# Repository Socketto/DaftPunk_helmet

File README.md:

# Project Overview

This project consists of two interconnected boards using the I2C protocol. The main board, equipped with a PIC microcontroller, controls RGB LEDs (used in the mask project for the ears) and a series of MCP23017 IO extenders for the screen positioned in front of the eyes.

Additionally, a 24LC256 EEPROM is included to store phrases to be displayed, which would otherwise be too short due to memory limitations.

## Programming and Interfaces

The board is programmed using a PicKit via an ICSP connector and can interface with RS485 networks or via an HC-06 module (Bluetooth).

## Android App Integration

The repository also includes a simple Android project that allows the board to be controlled via a smartphone. Through the app, users can:
- Display custom text on the screen
- Change the status of the RGB LEDs

[helmet](https://www.facebook.com/100001224670164/videos/a.159338040783684/2948037965246997?locale=it_IT)

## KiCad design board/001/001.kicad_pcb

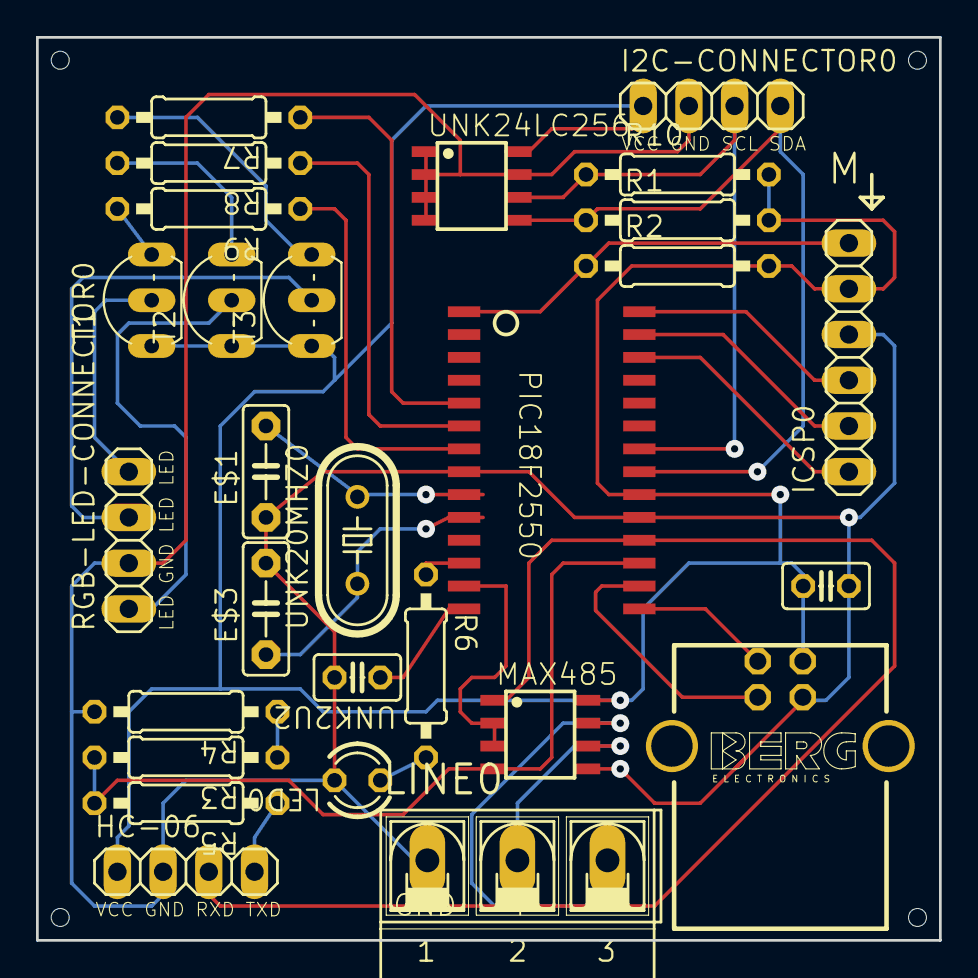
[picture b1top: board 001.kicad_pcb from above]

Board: 2 copper layers, 50.2 x 50.2 mm, 32 parts (0 on the bottom side), 10 nets.

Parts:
E$1, E$3: C5B2.5_116
HC-06: 1X04_325
I2C-CONNECTOR0: 1X04_325
ICSP0: 1X06_325
LED0: LED3MM_259
LINE0: AK500_3-H_181
MAX485: M8_279
PIC18F2550: SOIC28-3_206
R1, R2, R10: 10k; 0207_10_217
R3, R4, R5: 1k; 0207_10_217
R6, R7, R8, R9: 470; 0207_10_217
RGB-LED-CONNECTOR0: 1X04_325
T1, T2, T3: BC640; TO92-BCE_399
UNK2U2, UNK220UF0: C025-025X050_334
UNK20MHZ0: HC49_S_204
UNK24LC256: M8_279
UNK_HOLE_0: dummyfp0
UNK_HOLE_1: dummyfp1
UNK_HOLE_2: dummyfp2
UNK_HOLE_3: dummyfp3
USB0: PN61729-S_130

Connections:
S$1: R3.2, R5.2
S$2: HC-06.1, HC-06.2, I2C-CONNECTOR0.1, LED0.K, R4.2, R7.1, R8.1, R9.1, RGB-LED-CONNECTOR0.2, UNK2U2.2
S$5: I2C-CONNECTOR0.4, R1.1
S$12: R7.2, T3.B
S$16: R1.2, R10.2
S$23: R8.2, T2.B
S$25: HC-06.4, R5.1
S$27: R9.2, T1.B
S$29: RGB-LED-CONNECTOR0.1, T2.C
S$32: R3.1, R4.1

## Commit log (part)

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2025-03-07 [ADD] First commit
2025-03-07 [ADD] Add compilation of firmware
2025-03-07 Rename dotnet-desktop.yml to build-desktop.yml
2025-03-08 [FIX] Try fix compilation error with old compiler XC8
2025-03-09 Rename mplab-x_2.yml to mplab-x.yml
2025-03-10 [FIX] clean solution xc8
2025-03-11 [ADD] Add minimal firmware
2025-03-11 [UPD] Update readme.md
2025-04-18 [UPD] Update gitignore
2025-04-18 [UPD] Update boards
2026-02-22 [FIX] Start mask with online status (app not necessary)
